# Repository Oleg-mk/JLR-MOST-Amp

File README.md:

# Bitline

A stand-in for the stock JLR MOST25 amplifier. It takes the digital sound off the ring, carries out the head unit's
commands with no loss of quality and sends the sound on to your own DAC or amplifier. A phone joins over Bluetooth or
AirPlay.

Українською: [README.uk.md](README.uk.md).

Jaguar, Land Rover and JLR are trademarks of their owners. This project is not affiliated with them.

## What it is for

- Fit your own DAC and amplifier and keep the stock head unit with all its controls: volume, tone, mute, navigation,
  phone, parking sensors and chimes.
- Play a phone through the same system, with no cables.

## Cars

- JLR MOST25 stock amplifiers of two generations. The pre-facelift Hi-Line and Premium are the same amplifier in Jaguar
  and Land Rover, set up for the car. AUD3-8, -12 and -16 (Meridian) look the same on the bus. SW1 selects the type.
- First car: Jaguar XF X250, 2009.
- Component protection (Land Rover, Range Rover): the device reads the stock amplifier's serial number and the rest of
  how it answers the head unit, and then answers the same way.

## What it does

- **Sound from the ring.** 48 kHz, 16 bit. Pre-facelift: sinks 1-4 carry stereo music; phone, navigation and voice;
  parking sensors; chimes. AUD3: main or video (stereo), call, parking sensors, navigation. They are mixed down to
  stereo, as the stock amplifier does.
- **Head unit commands.** Levels per sink (volume), balance, mute with the ramps from MuteParameters, bass, treble.
  Processing in float, 24-bit out; at neutral settings the sound passes bit for bit.
- **Outputs**, all at once, one stream:
  - line RCA, 2.1 Vrms, straight from a PCM5122 DAC, no op-amp;
  - I2S with MCLK over HDMI for an external DAC: LVDS, PS Audio pinout;
  - S/PDIF: TOSLINK and 0.5 V coax into 75 ohm;
  - REM +12 V for an external amplifier.
- **Phone.** Bluetooth A2DP from any phone, with pause and volume over AVRCP; lossless AirPlay from an iPhone over the
  phone's hotspot. The phone's sound follows the ring's clock.
- **Switching.** The phone plays while the head unit is on a quiet source (AUX or paused). When the head unit plays, the
  phone pauses; when it goes quiet, the phone plays again. Of two phones, the newer one plays.
- **Updates over Wi-Fi** with a trial start and a return to the previous firmware if the new one does not take: it
  crashes, does not keep the network, the page or the sound path, or the ring chip does not start with it.
- **Start and sleep.** Joins the ring as the stock amplifier would. Sleeps on the network master's command, when the
  ring's light goes or when the ring chip stops answering; wakes on light.

## Hardware

- ESP32-WROVER-IE: 16 MB flash, 8 MB PSRAM, Bluetooth, Wi-Fi, external antenna connector.
- OS8104A, the MOST node: control, ring sound, clocks, S/PDIF.
- PCM5122, the line-out DAC.
- Optics: TE 1-1394640-1; the ring's plug goes straight into it.
- Power: +12 V from the stock amplifier's connector. Asleep, only the standby LDO and the optical receiver are on.
- An optional tube board stacks on the main one on standoffs and takes the DAC's line out: four 6N28B-V or 6N16B-V as an
  amplifier stage, a concertina and followers, no transformer; XLR and RCA out. Its anode supply comes about 12 s after
  REM, and about 9 s later it switches on the external amplifier's REM; on the way down that goes first.
- **Bitline Lite** is the same main board without the DAC, RCA L/R, HDMI, REM and USB (51 parts not fitted): the car
  keeps its ring, the sound leaves over TOSLINK and coax. It is flashed once through the J3 header, then over Wi-Fi.
  `hw/gen/lite.py` makes its package, LCSC numbers included.

## Status

- **Firmware.** The amplifier emulation, processing, phone, Wi-Fi, AirPlay, switching, profiles, the serial number
  read, updates and sleep are checked on a virtual model (QEMU) by test scripts, and what depends on the ring chip by
  tests on a PC with stubs for the hardware. The emulation has been reconciled function by function with usb2most's
  code, and the self-tests take their reference bytes from its firmware
  ([docs/usb2most/check_amp.md](docs/usb2most/check_amp.md)). The board on the bench, the ring in a car, ring sound to
  the outputs and REM are still to be checked on a real board.
- **Boards.** The 2- and 4-layer main boards and the tube board are ready to order; none has been made or tested yet.
  The main board has been checked pin by pin against the datasheets, its ring part also against usb2most's schematic
  ([docs/board_check/check.md](docs/board_check/check.md)). What only a live board can show is listed there as well.

## Repository map

| Path | What |
|---|---|
| `fw/` | firmware, ESP-IDF v5.5.6, C |
| `fw/tools/` | PC scripts that play the ring, a phone, an iPhone and the head unit for the firmware in QEMU; `host/` has tests that run on a PC without an ESP32 |
| `hw/` | main board, 2 layers, KiCad 10: schematic and board; `gen/` holds the generators and checks, `production/` the files for JLCPCB |
| `hw4/` | the same board on 4 layers |
| `tube/` | the tube board: `6n28b/` (board and package), `6n16b/` (schematic and BOM for 6N16B-V on the same board), `gen/` |
| `docs/` | concept, block diagram, stock amplifiers, firmware plan and log, the reconciliation with usb2most, the datasheet check of the main board |
| `ref/usb2most/` | reference files from [usb2most](https://github.com/smartgauges/usb2most), GPL-3.0 |

## Build

Firmware:

1. Install ESP-IDF v5.5.6. The path to `fw` must be in Latin letters, without spaces.
2. In `fw`: `idf.py build`. The first build fetches espressif/mdns 1.14.1 from the Espressif registry.
3. Flash with `idf.py -p COM5 flash monitor` over the board's USB-C. On the bench without a ring, hold SW2 for the whole
   write: it powers the board without light on the ring. Bitline Lite has no USB: a 3.3 V USB-UART adapter goes on J3
   (pin 1 IO0 to ground for the write, 2 GND, 3 RXD0, 4 TXD0) and esptool runs with `--before no_reset --after no_reset`.

Virtual model: `idf.py -B build_qemu -DQEMU=1 build`, then `idf.py -B build_qemu qemu`. PC tests:
`python tools/host/run.py`, which needs GCC MinGW-w64. `tools/host/golden.py` makes `main/u2m_golden.h` from usb2most's
firmware; that binary is not in this repository ([ref/usb2most/README.md](ref/usb2most/README.md)), and without it
`run.py` says the header was not compared and goes on.

Boards: KiCad 10. Every `production/` folder has a README with the JLCPCB order fields; `hw/gen/fab.py` regenerates
the files.

## Licence

Copyright 2026 Oleg-mk.

- **Hardware, under CERN-OHL-S-2.0** ([LICENSE](LICENSE)): `hw/`, `hw4/` and `tube/`: the KiCad designs and the
  scripts that generate them, footprints, 3D models, fabrication files.
- **Software and its documentation, under GPL-3.0-or-later** ([COPYING](COPYING)): `fw/` and `docs/`.
- **Other people's parts keep their licences:** Apple's ALAC decoder in `fw/components/alac/` (Apache-2.0,
  `APPLE_LICENSE.txt`); the AirPort key in `fw/main/raop_key.c` as shairport-sync carries it (MIT); `ref/usb2most/`
  (GPL-3.0); footprints and 3D models from other sources as `hw/SOURCES.md` lists them.

If you build or change the hardware and share it, share your sources under the same licence.

## How it was made

The author made the decisions, placed the parts and routed much of the copper. Claude (Anthropic's AI model, in
Claude Code) wrote the firmware, the schematic generators, the checks and the rest of the copper, as a co-author.

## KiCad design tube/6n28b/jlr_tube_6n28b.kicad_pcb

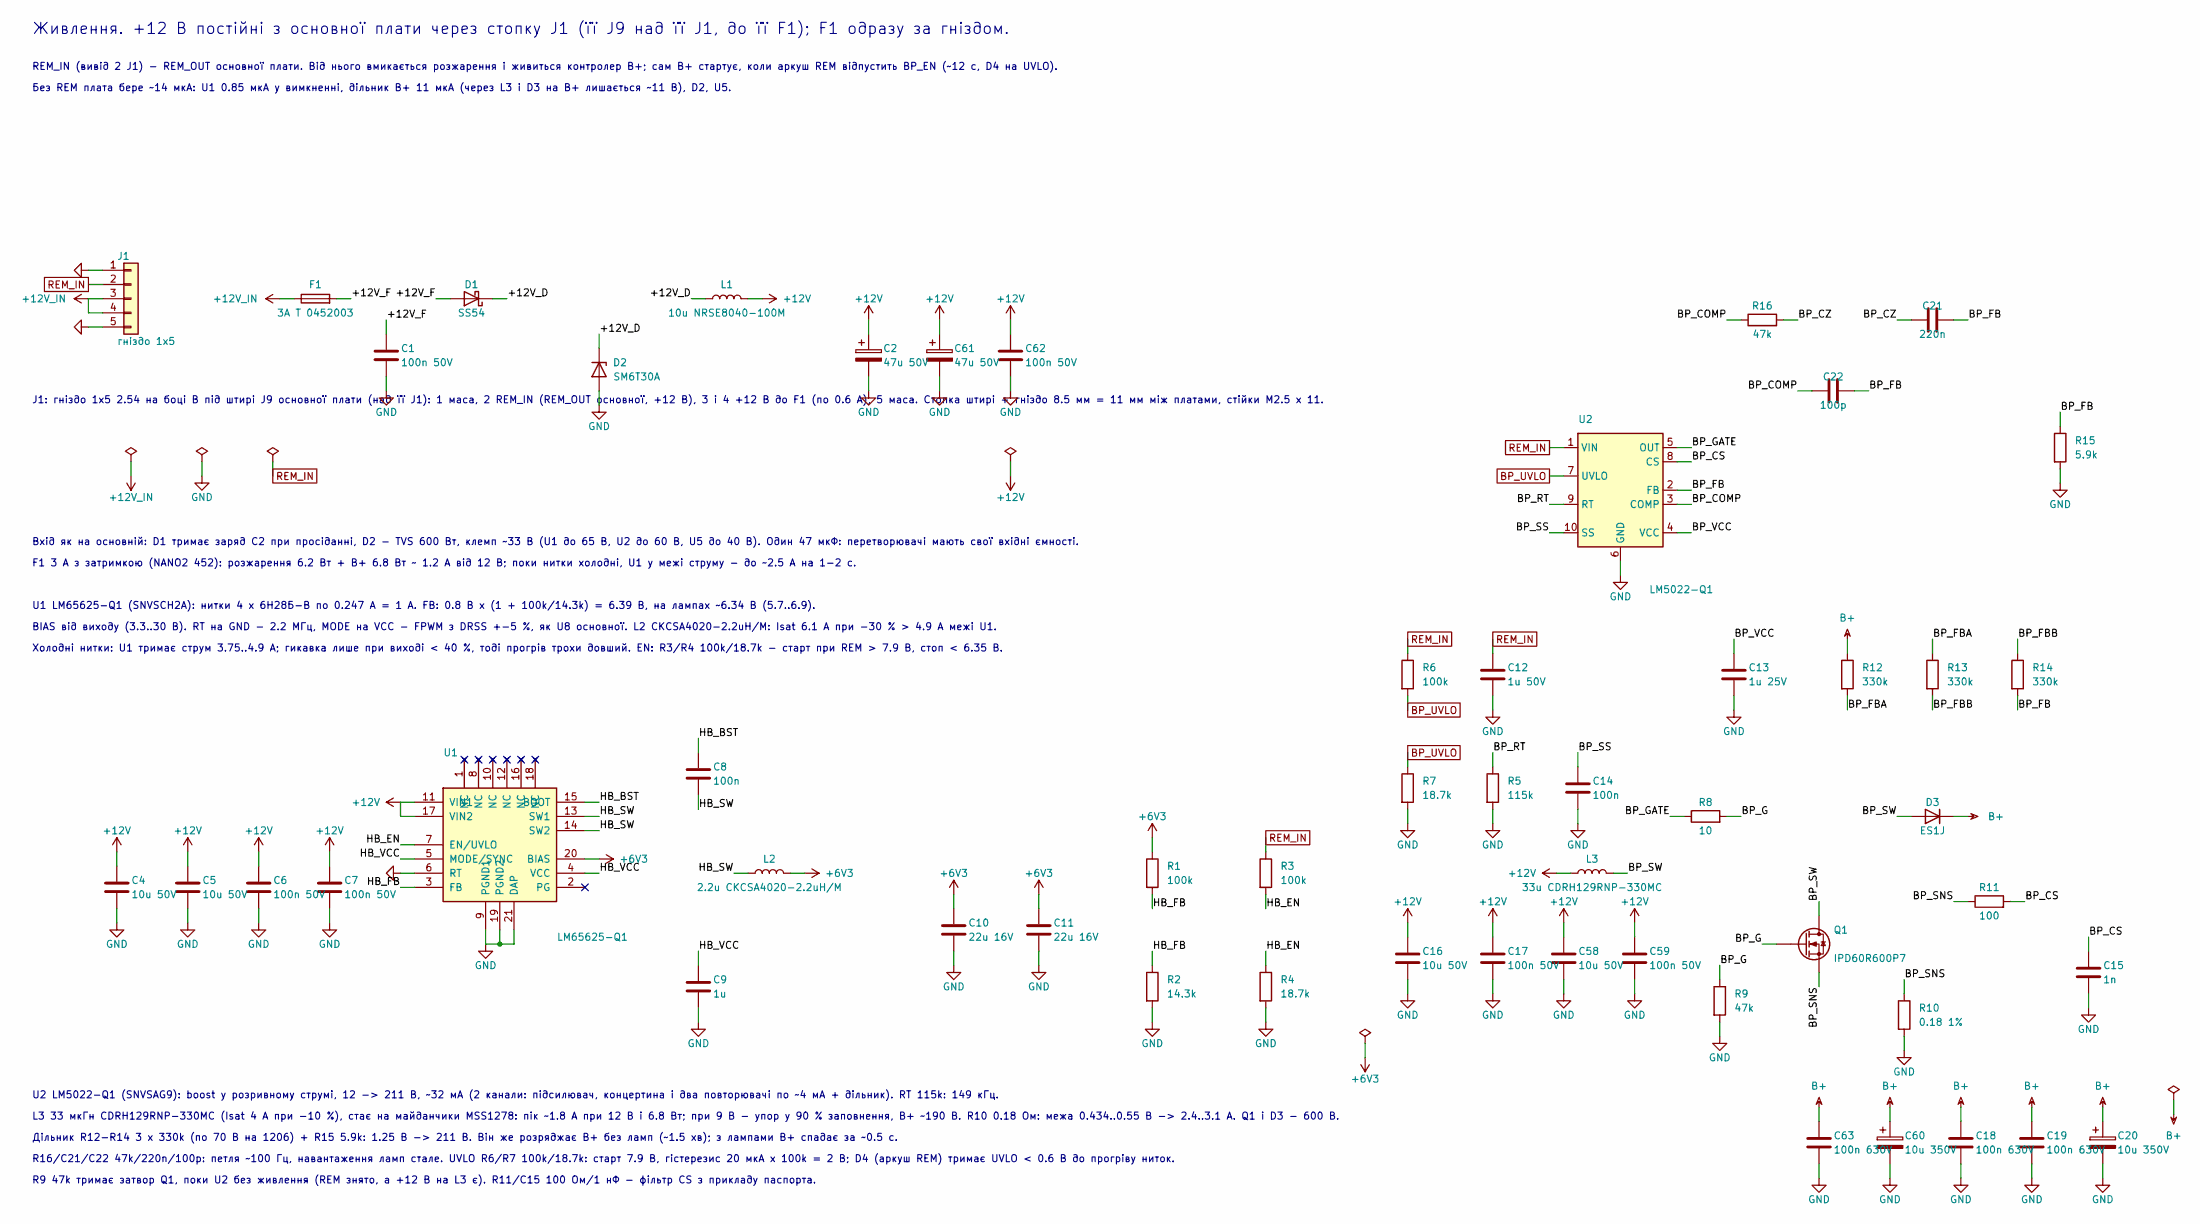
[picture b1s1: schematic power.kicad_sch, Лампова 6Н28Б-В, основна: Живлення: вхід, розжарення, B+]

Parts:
C1, C17, C59, C62: 100n 50V; C_0805_2012Metric
C2, C61: 47u 50V; CP_Elec_8x10
C4, C5, C16, C58: 10u 50V; C_1210_3225Metric
C6, C7: 100n 50V; C_0603_1608Metric
C8: 100n; C_0603_1608Metric
C9: 1u; C_0603_1608Metric
C10, C11: 22u 16V; C_1206_3216Metric
C12: 1u 50V; C_0805_2012Metric
C13: 1u 25V; C_0805_2012Metric
C14: 100n; C_0805_2012Metric
C15: 1n; C_0805_2012Metric
C18, C19, C63: 100n 630V; C_1812_4532Metric
C20, C60: 10u 350V; CP_Radial_D10.0mm_P5.00mm
C21: 220n; C_0805_2012Metric
C22: 100p; C_0805_2012Metric
D1: SS54; D_SMC
D2: SM6T30A; D_SMB
D3: ES1J; D_SMA
F1: 3A T 0452003; Fuse_Littelfuse-NANO2-451_453
J1: гніздо 1x5; PinSocket_1x05_P2.54mm_Vertical
L1: 10u NRSE8040-100M; L_Bourns-SRN8040_8x8.15mm
L2: 2.2u CKCSA4020-2.2uH/M; L_Coilcraft_XxL4030
L3: 33u CDRH129RNP-330MC; L_Coilcraft_MSS1278-XXX
Q1: IPD60R600P7; TO-252-2
R1, R3, R6: 100k; R_0805_2012Metric
R2: 14.3k; R_0805_2012Metric
R4, R7: 18.7k; R_0805_2012Metric
R5: 115k; R_0805_2012Metric
R8: 10; R_0805_2012Metric
R9, R16: 47k; R_0805_2012Metric
R10: 0.18 1%; R_1206_3216Metric
R11: 100; R_0805_2012Metric
R12, R13, R14: 330k; R_1206_3216Metric
R15: 5.9k; R_0805_2012Metric
U1: LM65625-Q1; TI_RZT0020A
U2: LM5022-Q1; MSOP-10_3x3mm_P0.5mm

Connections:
+6V3: C10.1, C11.1, L2.2, R1.1, U1.20 (BIAS); also elsewhere on the board
+12V: C2.1, C4.1, C5.1, C6.1, C7.1, C16.1, C17.1, C58.1, C59.1, C61.1, C62.1, L1.2, L3.1, U1.11 (VIN1), U1.17 (VIN2); also elsewhere on the board
+12V_IN: F1.1, J1.3, J1.4
/Живлення: вхід, розжарення, B+/+12V_D: D1.1 (K), D2.1 (K), L1.1
/Живлення: вхід, розжарення, B+/+12V_F: C1.1, D1.2 (A), F1.2
/Живлення: вхід, розжарення, B+/BP_COMP: C22.1, R16.1, U2.3 (COMP)
/Живлення: вхід, розжарення, B+/BP_CS: C15.1, R11.2, U2.8 (CS)
/Живлення: вхід, розжарення, B+/BP_CZ: C21.1, R16.2
/Живлення: вхід, розжарення, B+/BP_FB: C21.2, C22.2, R14.2, R15.1, U2.2 (FB)
/Живлення: вхід, розжарення, B+/BP_FBA: R12.2, R13.1
/Живлення: вхід, розжарення, B+/BP_FBB: R13.2, R14.1
/Живлення: вхід, розжарення, B+/BP_G: Q1.1 (G), R8.2, R9.1
/Живлення: вхід, розжарення, B+/BP_GATE: R8.1, U2.5 (OUT)
/Живлення: вхід, розжарення, B+/BP_RT: R5.1, U2.9 (RT)
/Живлення: вхід, розжарення, B+/BP_SNS: Q1.3 (S), R10.1, R11.1
/Живлення: вхід, розжарення, B+/BP_SS: C14.1, U2.10 (SS)
/Живлення: вхід, розжарення, B+/BP_SW: D3.2 (A), L3.2, Q1.2 (D)
/Живлення: вхід, розжарення, B+/BP_VCC: C13.1, U2.4 (VCC)
/Живлення: вхід, розжарення, B+/HB_BST: C8.1, U1.15 (BOOT)
/Живлення: вхід, розжарення, B+/HB_EN: R3.2, R4.1, U1.7 (EN/UVLO)
/Живлення: вхід, розжарення, B+/HB_FB: R1.2, R2.1, U1.3 (FB)
/Живлення: вхід, розжарення, B+/HB_SW: C8.2, L2.1, U1.13 (SW1), U1.14 (SW2)
/Живлення: вхід, розжарення, B+/HB_VCC: C9.1, U1.4 (VCC), U1.5 (MODE/SYNC)
B+: C18.1, C19.1, C20.1, C60.1, C63.1, D3.1 (K), R12.1; also elsewhere on the board
BP_UVLO: R6.2, R7.1, U2.7 (UVLO); also elsewhere on the board
GND: C1.2, C2.2, C4.2, C5.2, C6.2, C7.2, C9.2, C10.2, C11.2, C12.2, C13.2, C14.2, C15.2, C16.2, C17.2, C18.2, C19.2, C20.2, C58.2, C59.2, C60.2, C61.2, C62.2, C63.2, D2.2 (A), J1.1, J1.5, R2.2, R4.2, R5.2, R7.2, R9.2, R10.2, R15.2, U1.6 (RT), U1.9 (PGND1), U1.19 (PGND2), U1.21 (DAP), U2.6 (GND); also elsewhere on the board
REM_IN: C12.1, J1.2, R3.1, R6.1, U2.1 (VIN); also elsewhere on the board

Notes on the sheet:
Живлення. +12 В постійні з основної плати через стопку J1 (її J9 над її J1, до її F1); F1 одразу за гніздом.
REM_IN (вивід 2 J1) - REM_OUT основної плати. Від нього вмикається розжарення і живиться контролер B+; сам B+ стартує, коли аркуш REM відпустить BP_EN (~12 с, D4 на UVLO).
Без REM плата бере ~14 мкА: U1 0.85 мкА у вимкненні, дільник B+ 11 мкА (через L3 і D3 на B+ лишається ~11 В), D2, U5.
J1: гніздо 1x5 2.54 на боці B під штирі J9 основної плати (над її J1): 1 маса, 2 REM_IN (REM_OUT основної, +12 В), 3 і 4 +12 В до F1 (по 0.6 А), 5 маса. Стопка штирі + гніздо 8.5 мм = 11 мм між платами, стійки M2.5 x 11.
Вхід як на основній: D1 тримає заряд C2 при просіданні, D2 - TVS 600 Вт, клемп ~33 В (U1 до 65 В, U2 до 60 В, U5 до 40 В). Один 47 мкФ: перетворювачі мають свої вхідні ємності.
F1 3 А з затримкою (NANO2 452): розжарення 6.2 Вт + B+ 6.8 Вт ~ 1.2 А від 12 В; поки нитки холодні, U1 у межі струму - до ~2.5 А на 1-2 с.
U1 LM65625-Q1 (SNVSCH2A): нитки 4 x 6Н28Б-В по 0.247 А = 1 А. FB: 0.8 В x (1 + 100k/14.3k) = 6.39 В, на лампах ~6.34 В (5.7..6.9).
BIAS від виходу (3.3..30 В). RT на GND - 2.2 МГц, MODE на VCC - FPWM з DRSS +-5 %, як U8 основної. L2 CKCSA4020-2.2uH/M: Isat 6.1 А при -30 % > 4.9 А межі U1.
Холодні нитки: U1 тримає струм 3.75..4.9 А; гикавка лише при виході < 40 %, тоді прогрів трохи довший. EN: R3/R4 100k/18.7k - старт при REM > 7.9 В, стоп < 6.35 В.
U2 LM5022-Q1 (SNVSAG9): boost у розривному струмі, 12 -> 211 В, ~32 мА (2 канали: підсилювач, концертина і два повторювачі по ~4 мА + дільник). RT 115k: 149 кГц.
L3 33 мкГн CDRH129RNP-330MC (Isat 4 А при -10 %), стає на майданчики MSS1278: пік ~1.8 А при 12 В і 6.8 Вт; при 9 В - упор у 90 % заповнення, B+ ~190 В. R10 0.18 Ом: межа 0.434..0.55 В -> 2.4..3.1 А. Q1 і D3 - 600 В.
Дільник R12-R14 3 x 330k (по 70 В на 1206) + R15 5.9k: 1.25 В -> 211 В. Він же розряджає B+ без ламп (~1.5 хв); з лампами B+ спадає за ~0.5 с.
R16/C21/C22 47k/220n/100p: петля ~100 Гц, навантаження ламп стале. UVLO R6/R7 100k/18.7k: старт 7.9 В, гістерезис 20 мкА x 100k = 2 В; D4 (аркуш REM) тримає UVLO < 0.6 В до прогріву ниток.
R9 47k тримає затвор Q1, поки U2 без живлення (REM знято, а +12 В на L3 є). R11/C15 100 Ом/1 нФ - фільтр CS з прикладу паспорта.

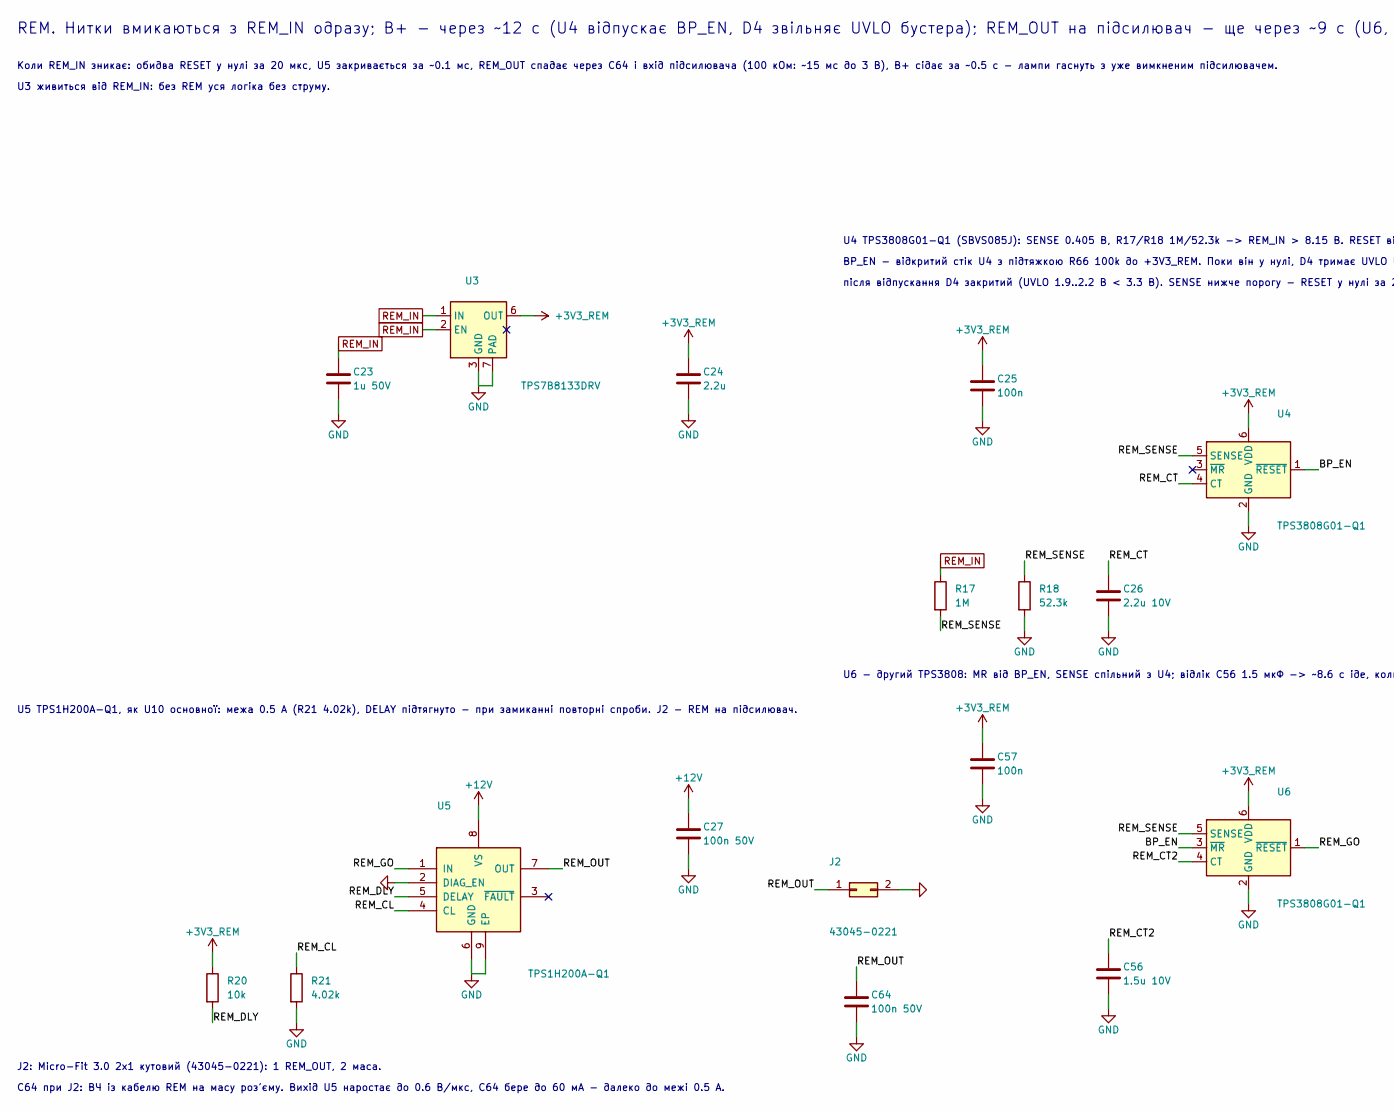
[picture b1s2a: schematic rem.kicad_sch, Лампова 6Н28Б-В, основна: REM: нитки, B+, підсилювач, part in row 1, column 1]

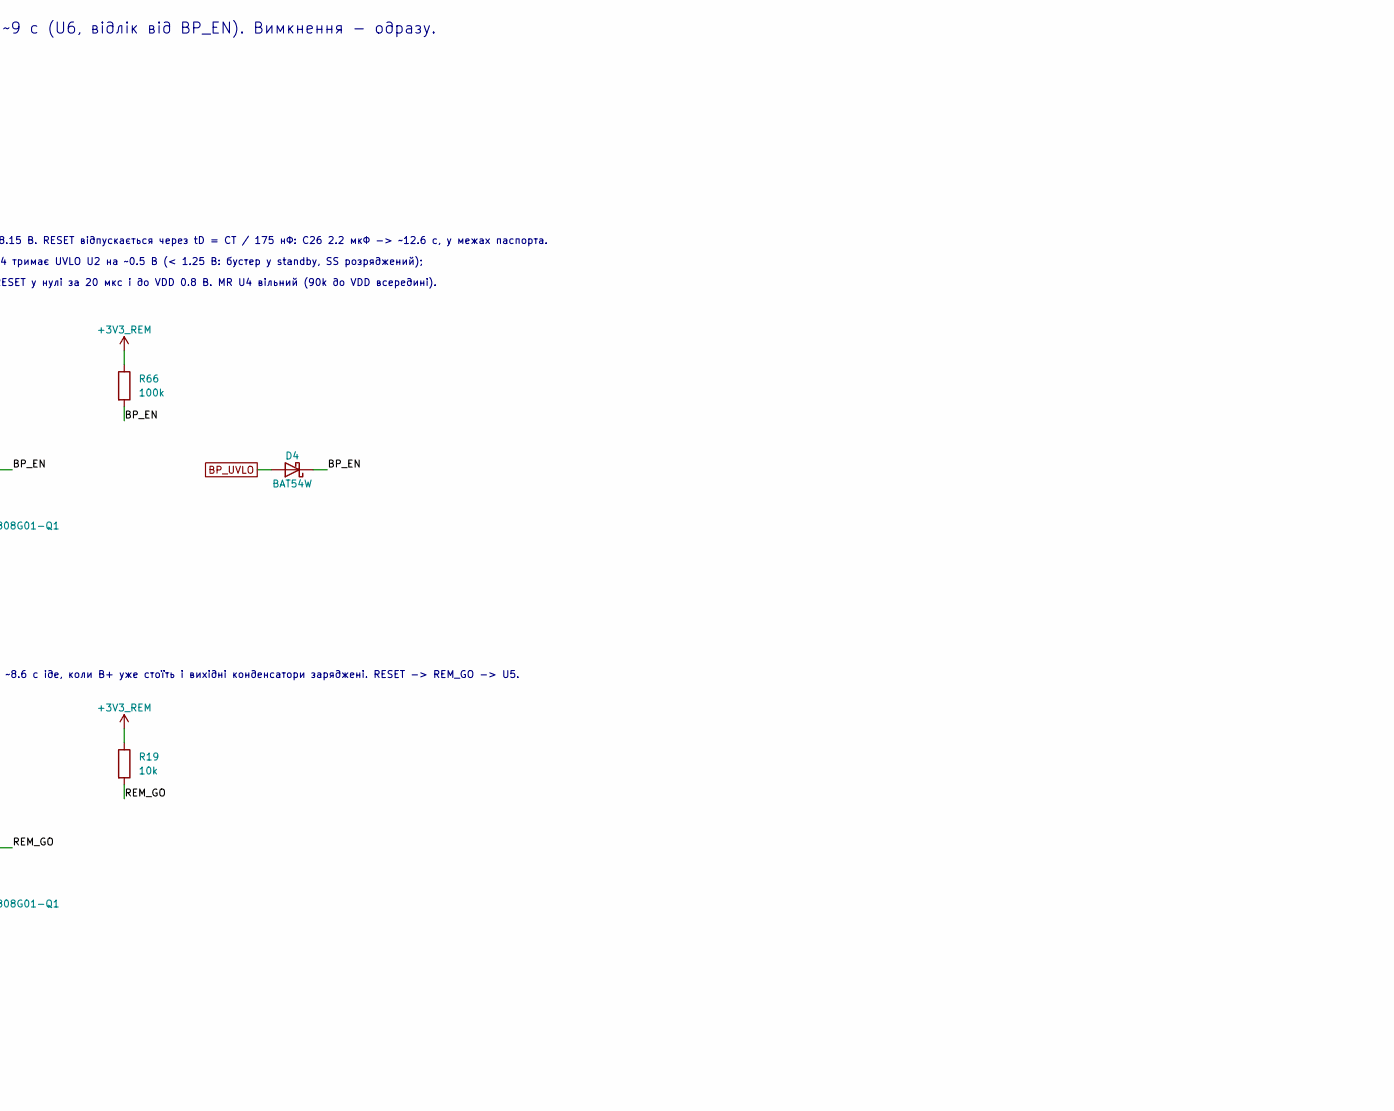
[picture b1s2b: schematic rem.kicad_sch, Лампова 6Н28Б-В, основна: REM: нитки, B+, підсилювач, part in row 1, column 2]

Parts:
C23: 1u 50V; C_0805_2012Metric
C24: 2.2u; C_0805_2012Metric
C25, C57: 100n; C_0805_2012Metric
C26: 2.2u 10V; C_0805_2012Metric
C27, C64: 100n 50V; C_0805_2012Metric
C56: 1.5u 10V; C_0805_2012Metric
D4: BAT54W; D_SOD-123
J2: 43045-0221; Molex_Micro-Fit_3.0_43045-0221_2x01-1MP_P3.00mm_Horizontal
R17: 1M; R_0805_2012Metric
R18: 52.3k; R_0805_2012Metric
R19, R20: 10k; R_0805_2012Metric
R21: 4.02k; R_0805_2012Metric
R66: 100k; R_0805_2012Metric
U3: TPS7B8133DRV; WSON-6-1EP_2x2mm_P0.65mm_EP1x1.6mm
U4, U6: TPS3808G01-Q1; SOT-23-6
U5: TPS1H200A-Q1; HVSSOP-8-1EP_3x3mm_P0.65mm_EP1.57x1.89mm

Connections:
+3V3_REM: C24.1, C25.1, C57.1, R19.1, R20.1, R66.1, U3.6 (OUT), U4.6 (VDD), U6.6 (VDD)
+12V: C27.1, U5.8 (VS); also elsewhere on the board
/REM: нитки, B+, підсилювач/BP_EN: D4.1 (K), R66.2, U4.1 (~RESET), U6.3 (~MR)
/REM: нитки, B+, підсилювач/REM_CL: R21.1, U5.4 (CL)
/REM: нитки, B+, підсилювач/REM_CT: C26.1, U4.4 (CT)
/REM: нитки, B+, підсилювач/REM_CT2: C56.1, U6.4 (CT)
/REM: нитки, B+, підсилювач/REM_DLY: R20.2, U5.5 (DELAY)
/REM: нитки, B+, підсилювач/REM_GO: R19.2, U5.1 (IN), U6.1 (~RESET)
/REM: нитки, B+, підсилювач/REM_OUT: C64.1, J2.1, U5.7 (OUT)
/REM: нитки, B+, підсилювач/REM_SENSE: R17.2, R18.1, U4.5 (SENSE), U6.5 (SENSE)
BP_UVLO: D4.2 (A); also elsewhere on the board
GND: C23.2, C24.2, C25.2, C26.2, C27.2, C56.2, C57.2, C64.2, J2.2, R18.2, R21.2, U3.3 (GND), U3.4 (GND), U3.7 (PAD), U4.2 (GND), U5.2 (DIAG_EN), U5.6 (GND), U5.9 (EP), U6.2 (GND); also elsewhere on the board
REM_IN: C23.1, R17.1, U3.1 (IN), U3.2 (EN); also elsewhere on the board

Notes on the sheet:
REM. Нитки вмикаються з REM_IN одразу; B+ - через ~12 с (U4 відпускає BP_EN, D4 звільняє UVLO бустера); REM_OUT на підсилювач - ще через ~9 с (U6, відлік від BP_EN). Вимкнення - одразу.
Коли REM_IN зникає: обидва RESET у нулі за 20 мкс, U5 закривається за ~0.1 мс, REM_OUT спадає через C64 і вхід підсилювача (100 кОм: ~15 мс до 3 В), B+ сідає за ~0.5 с - лампи гаснуть з уже вимкненим підсилювачем.
U3 живиться від REM_IN: без REM уся логіка без струму.
U4 TPS3808G01-Q1 (SBVS085J): SENSE 0.405 В, R17/R18 1M/52.3k -> REM_IN > 8.15 В. RESET відпускається через tD = CT / 175 нФ: C26 2.2 мкФ -> ~12.6 с, у межах паспорта.
BP_EN - відкритий стік U4 з підтяжкою R66 100k до +3V3_REM. Поки він у нулі, D4 тримає UVLO U2 на ~0.5 В (< 1.25 В: бустер у standby, SS розряджений);
після відпускання D4 закритий (UVLO 1.9..2.2 В < 3.3 В). SENSE нижче порогу - RESET у нулі за 20 мкс і до VDD 0.8 В. MR U4 вільний (90k до VDD всередині).
U6 - другий TPS3808: MR від BP_EN, SENSE спільний з U4; відлік C56 1.5 мкФ -> ~8.6 с іде, коли B+ уже стоїть і вихідні конденсатори заряджені. RESET -> REM_GO -> U5.
U5 TPS1H200A-Q1, як U10 основної: межа 0.5 А (R21 4.02k), DELAY підтягнуто - при замиканні повторні спроби. J2 - REM на підсилювач.
J2: Micro-Fit 3.0 2x1 кутовий (43045-0221): 1 REM_OUT, 2 маса.
C64 при J2: ВЧ із кабелю REM на масу роз'єму. Вихід U5 наростає до 0.6 В/мкс, C64 бере до 60 мА - далеко до межі 0.5 А.

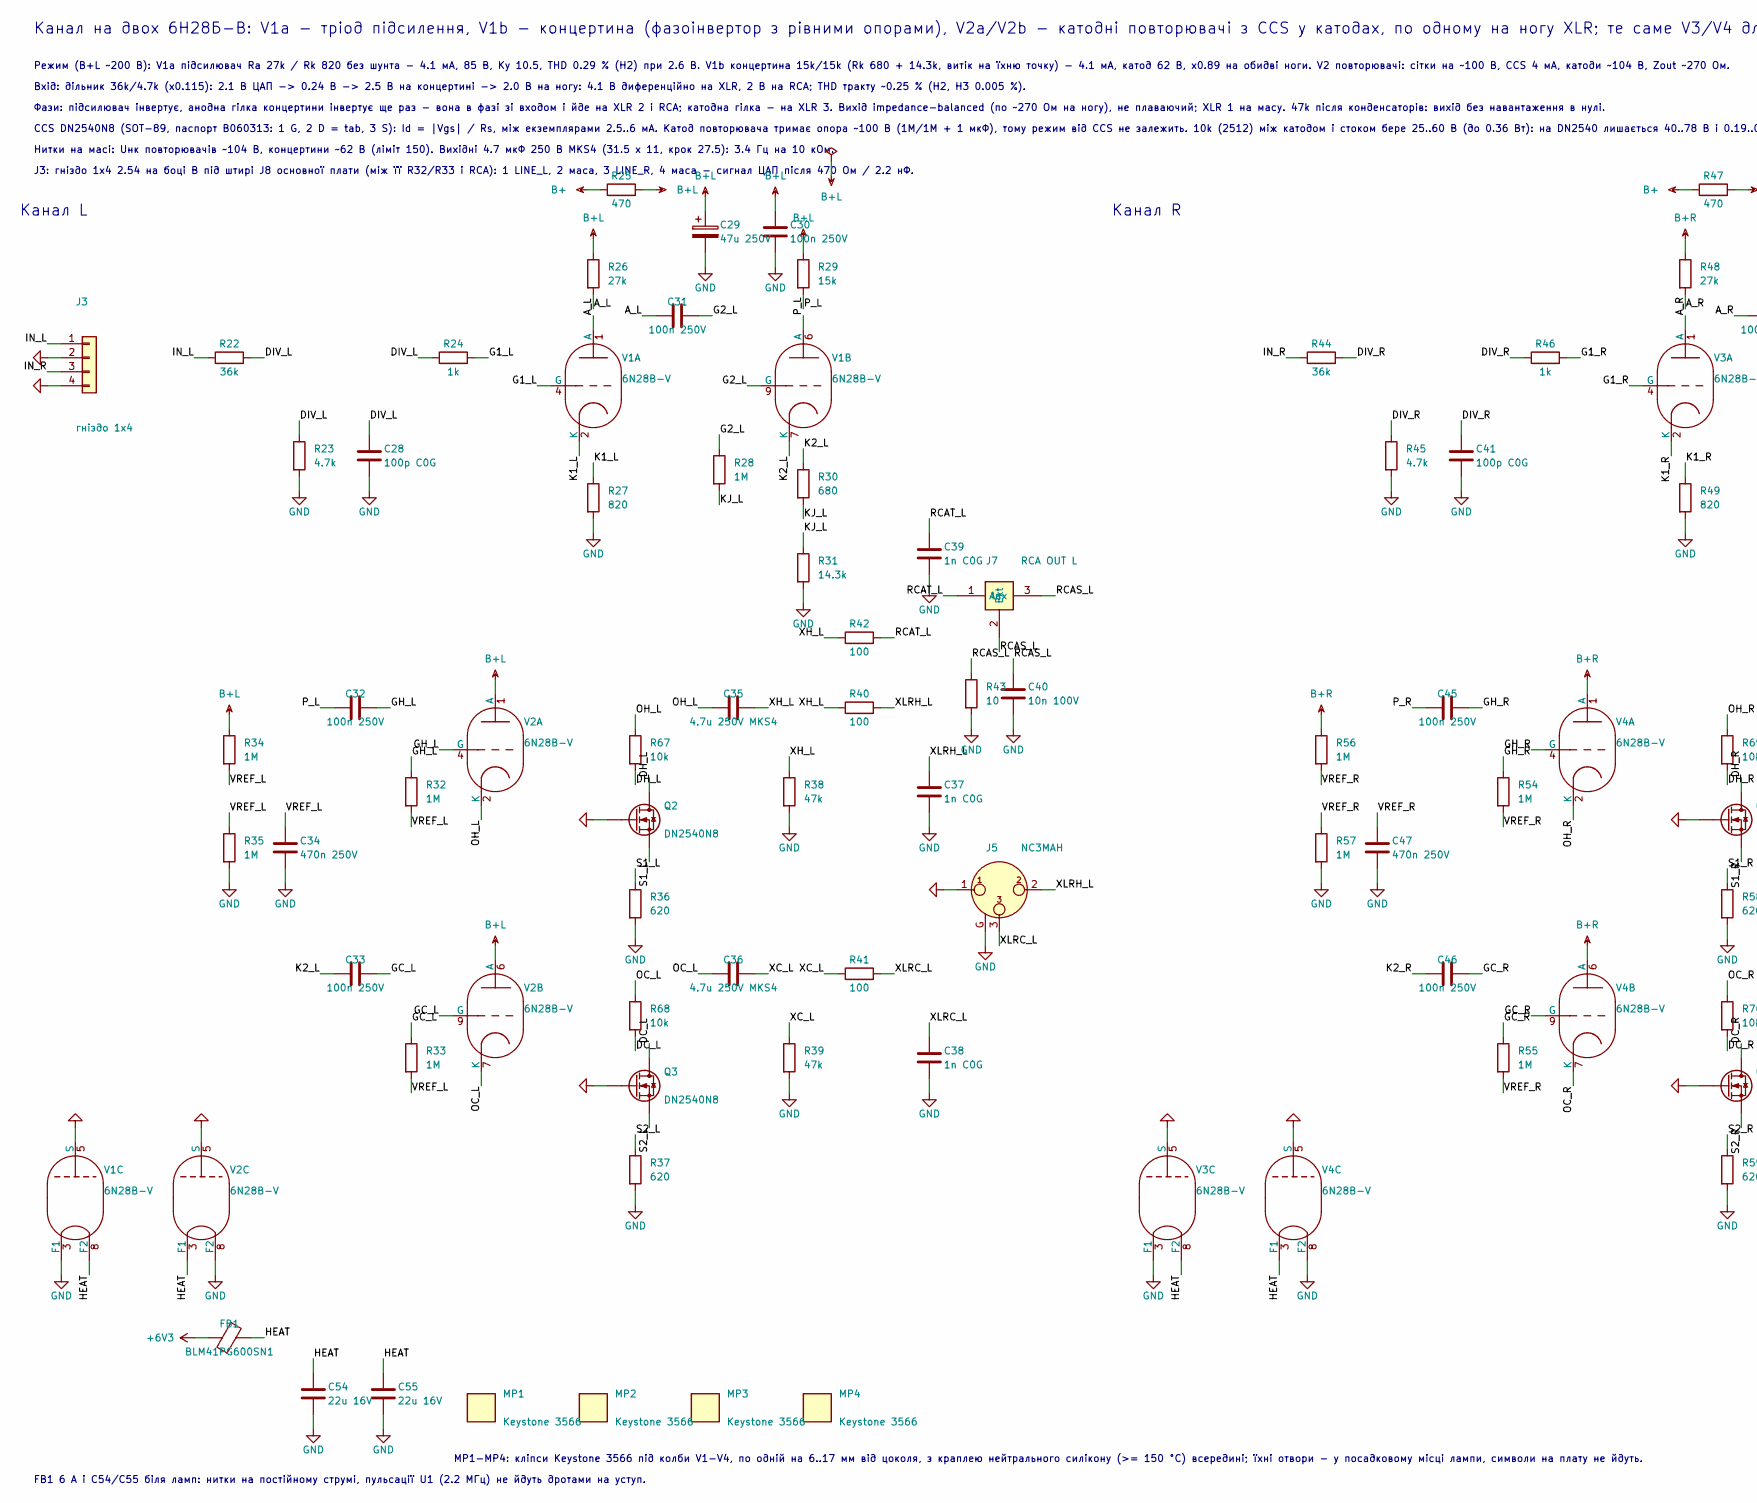
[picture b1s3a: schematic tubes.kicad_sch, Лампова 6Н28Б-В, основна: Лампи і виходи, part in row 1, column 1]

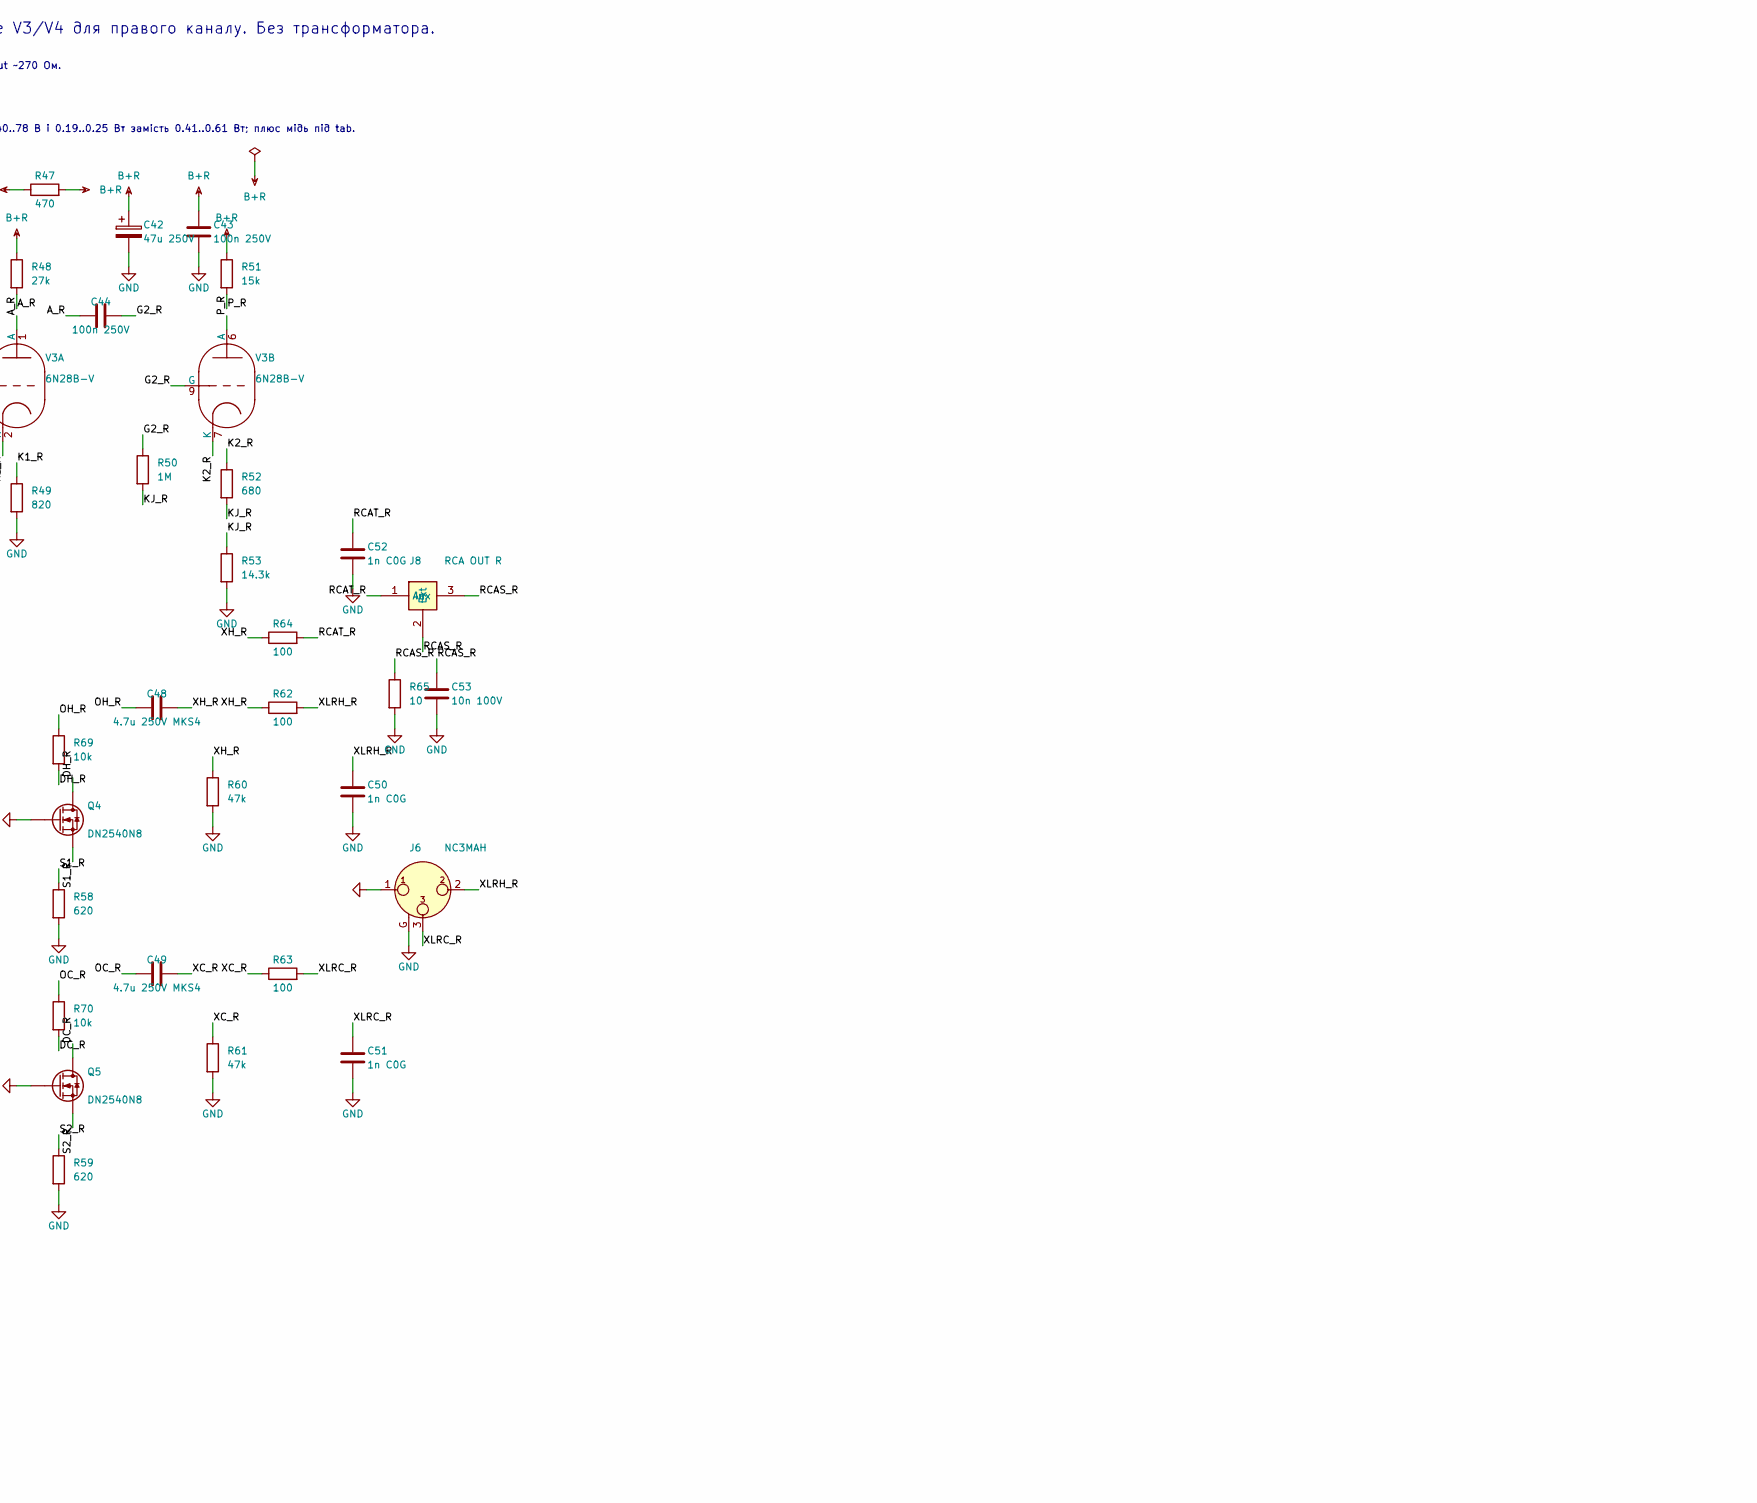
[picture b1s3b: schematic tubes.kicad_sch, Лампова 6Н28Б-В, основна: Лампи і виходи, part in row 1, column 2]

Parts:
C28, C41: 100p C0G; C_0805_2012Metric
C29, C42: 47u 250V; CP_Radial_D12.5mm_P5.00mm
C30, C43: 100n 250V; C_1206_3216Metric
C31, C32, C33, C44, C45, C46: 100n 250V; C_Rect_L7.2mm_W4.5mm_P5.00mm_FKS2_FKP2_MKS2_MKP2
C34, C47: 470n 250V; C_1210_3225Metric
C35, C36, C48, C49: 4.7u 250V MKS4; C_Rect_L31.5mm_W11.0mm_P27.50mm_MKS4
C37, C38, C39, C50, C51, C52: 1n C0G; C_0805_2012Metric
C40, C53: 10n 100V; C_0805_2012Metric
C54, C55: 22u 16V; C_1206_3216Metric
FB1: BLM41PG600SN1; L_1806_4516Metric
J3: гніздо 1x4; PinSocket_1x04_P2.54mm_Vertical
J5, J6: NC3MAH; Neutrik_NC3MAH
J7: RCA OUT L; BKL_0101153_RCA_RA
J8: RCA OUT R; BKL_0101153_RCA_RA
MP1, MP2, MP3, MP4: Keystone 3566
Q2, Q3, Q4, Q5: DN2540N8; SOT-89-3
R22, R44: 36k; R_0805_2012Metric
R23, R45: 4.7k; R_0805_2012Metric
R24, R46: 1k; R_0805_2012Metric
R25, R47: 470; R_1206_3216Metric
R26, R48: 27k; R_2512_6332Metric
R27, R49: 820; R_0805_2012Metric
R28, R32, R33, R34, R35, R50, R54, R55, R56, R57: 1M; R_1206_3216Metric
R29, R51: 15k; R_2512_6332Metric
R30, R52: 680; R_0805_2012Metric
R31, R53: 14.3k; R_2512_6332Metric
R36, R37, R58, R59: 620; R_0805_2012Metric
R38, R39, R60, R61: 47k; R_1206_3216Metric
R40, R41, R42, R62, R63, R64: 100; R_0805_2012Metric
R43, R65: 10; R_0805_2012Metric
R67, R68, R69, R70: 10k; R_2512_6332Metric
V1, V3: 6N28B-V; Valve_6N28B-V_Flat_458
V2, V4: 6N28B-V; Valve_6N28B-V_Flat

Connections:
+6V3: FB1.1; also elsewhere on the board
/Лампи і виходи/A_L: C31.1, R26.2, V1.1 (A)
/Лампи і виходи/A_R: C44.1, R48.2, V3.1 (A)
/Лампи і виходи/DC_L: Q3.2 (D), R68.2
/Лампи і виходи/DC_R: Q5.2 (D), R70.2
/Лампи і виходи/DH_L: Q2.2 (D), R67.2
/Лампи і виходи/DH_R: Q4.2 (D), R69.2
/Лампи і виходи/DIV_L: C28.1, R22.2, R23.1, R24.1
/Лампи і виходи/DIV_R: C41.1, R44.2, R45.1, R46.1
/Лампи і виходи/G1_L: R24.2, V1.4 (G)
/Лампи і виходи/G1_R: R46.2, V3.4 (G)
/Лампи і виходи/G2_L: C31.2, R28.1, V1.9 (G)
/Лампи і виходи/G2_R: C44.2, R50.1, V3.9 (G)
/Лампи і виходи/GC_L: C33.2, R33.1, V2.9 (G)
/Лампи і виходи/GC_R: C46.2, R55.1, V4.9 (G)
/Лампи і виходи/GH_L: C32.2, R32.1, V2.4 (G)
/Лампи і виходи/GH_R: C45.2, R54.1, V4.4 (G)
/Лампи і виходи/HEAT: C54.1, C55.1, FB1.2, V1.8 (F2), V2.3 (F1), V3.8 (F2), V4.3 (F1)
/Лампи і виходи/IN_L: J3.1, R22.1
/Лампи і виходи/IN_R: J3.3, R44.1
/Лампи і виходи/K1_L: R27.1, V1.2 (K)
/Лампи і виходи/K1_R: R49.1, V3.2 (K)
/Лампи і виходи/K2_L: C33.1, R30.1, V1.7 (K)
/Лампи і виходи/K2_R: C46.1, R52.1, V3.7 (K)
/Лампи і виходи/KJ_L: R28.2, R30.2, R31.1
/Лампи і виходи/KJ_R: R50.2, R52.2, R53.1
/Лампи і виходи/OC_L: C36.1, R68.1, V2.7 (K)
/Лампи і виходи/OC_R: C49.1, R70.1, V4.7 (K)
/Лампи і виходи/OH_L: C35.1, R67.1, V2.2 (K)
/Лампи і виходи/OH_R: C48.1, R69.1, V4.2 (K)
/Лампи і виходи/P_L: C32.1, R29.2, V1.6 (A)
/Лампи і виходи/P_R: C45.1, R51.2, V3.6 (A)
/Лампи і виходи/RCAS_L: C40.1, J7.2 (Ext), J7.3 (Aux), R43.1
/Лампи і виходи/RCAS_R: C53.1, J8.2 (Ext), J8.3 (Aux), R65.1
/Лампи і виходи/RCAT_L: C39.1, J7.1 (In), R42.2
/Лампи і виходи/RCAT_R: C52.1, J8.1 (In), R64.2
/Лампи і виходи/S1_L: Q2.3 (S), R36.1
/Лампи і виходи/S1_R: Q4.3 (S), R58.1
/Лампи і виходи/S2_L: Q3.3 (S), R37.1
/Лампи і виходи/S2_R: Q5.3 (S), R59.1
/Лампи і виходи/VREF_L: C34.1, R32.2, R33.2, R34.2, R35.1
/Лампи і виходи/VREF_R: C47.1, R54.2, R55.2, R56.2, R57.1
/Лампи і виходи/XC_L: C36.2, R39.1, R41.1
/Лампи і виходи/XC_R: C49.2, R61.1, R63.1
/Лампи і виходи/XH_L: C35.2, R38.1, R40.1, R42.1
/Лампи і виходи/XH_R: C48.2, R60.1, R62.1, R64.1
/Лампи і виходи/XLRC_L: C38.1, J5.3, R41.2
/Лампи і виходи/XLRC_R: C51.1, J6.3, R63.2
/Лампи і виходи/XLRH_L: C37.1, J5.2, R40.2
/Лампи і виходи/XLRH_R: C50.1, J6.2, R62.2
B+: R25.1, R47.1; also elsewhere on the board
B+L: C29.1, C30.1, R25.2, R26.1, R29.1, R34.1, V2.1 (A), V2.6 (A)
B+R: C42.1, C43.1, R47.2, R48.1, R51.1, R56.1, V4.1 (A), V4.6 (A)
GND: C28.2, C29.2, C30.2, C34.2, C37.2, C38.2, C39.2, C40.2, C41.2, C42.2, C43.2, C47.2, C50.2, C51.2, C52.2, C53.2, C54.2, C55.2, J3.2, J3.4, J5.1, J5.G, J6.1, J6.G, Q2.1 (G), Q3.1 (G), Q4.1 (G), Q5.1 (G), R23.2, R27.2, R31.2, R35.2, R36.2, R37.2, R38.2, R39.2, R43.2, R45.2, R49.2, R53.2, R57.2, R58.2, R59.2, R60.2, R61.2, R65.2, V1.3 (F1), V1.5 (S), V2.5 (S), V2.8 (F2), V3.3 (F1), V3.5 (S), V4.5 (S), V4.8 (F2); also elsewhere on the board

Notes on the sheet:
Канал на двох 6Н28Б-В: V1a - тріод підсилення, V1b - концертина (фазоінвертор з рівними опорами), V2a/V2b - катодні повторювачі з CCS у катодах, по одному на ногу XLR; те саме V3/V4 для правого каналу. Без трансформатора.
Режим (B+L ~200 В): V1a підсилювач Ra 27k / Rk 820 без шунта - 4.1 мА, 85 В, Ку 10.5, THD 0.29 % (H2) при 2.6 В. V1b концертина 15k/15k (Rk 680 + 14.3k, витік на їхню точку) - 4.1 мА, катод 62 В, x0.89 на обидві ноги. V2 повторювачі: сітки на ~100 В, CCS 4 мА, катоди ~104 В, Zout ~270 Ом.
Вхід: дільник 36k/4.7k (x0.115): 2.1 В ЦАП -> 0.24 В -> 2.5 В на концертині -> 2.0 В на ногу: 4.1 В диференційно на XLR, 2 В на RCA; THD тракту ~0.25 % (H2, H3 0.005 %).
Фази: підсилювач інвертує, анодна гілка концертини інвертує ще раз - вона в фазі зі входом і йде на XLR 2 і RCA; катодна гілка - на XLR 3. Вихід impedance-balanced (по ~270 Ом на ногу), не плаваючий; XLR 1 на масу. 47k після конденсаторів: вихід без навантаження в нулі.
CCS DN2540N8 (SOT-89, паспорт B060313: 1 G, 2 D = tab, 3 S): Id = |Vgs| / Rs, між екземплярами 2.5..6 мА. Катод повторювача тримає опора ~100 В (1M/1M + 1 мкФ), тому режим від CCS не залежить. 10k (2512) між катодом і стоком бере 25..60 В (до 0.36 Вт): на DN2540 лишається 40..78 В і 0.19..0.25 Вт з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
Нитки на масі: Uнк повторювачів ~104 В, концертини ~62 В (ліміт 150). Вихідні 4.7 мкФ 250 В MKS4 (31.5 x 11, крок 27.5): 3.4 Гц на 10 кОм.
Канал L
Канал R
J3: гніздо 1x4 2.54 на боці B під штирі J8 основної плати (між її R32/R33 і RCA): 1 LINE_L, 2 маса, 3 LINE_R, 4 маса - сигнал ЦАП після 470 Ом / 2.2 нФ.
MP1-MP4: кліпси Keystone 3566 під колби V1-V4, по одній на 6..17 мм від цоколя, з краплею нейтрального силікону (>= 150 °C) всередині; їхні отвори - у посадковому місці лампи, символи на плату не йдуть.
FB1 6 А і C54/C55 біля ламп: нитки на постійному струмі, пульсації U1 (2.2 МГц) не йдуть дротами на уступ.
